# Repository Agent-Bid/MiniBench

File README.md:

# MiniBench

A compact USB-C powered bench power supply board designed to provide common rail voltages directly from your laptop or a USB-C power adapter.

## Features
- **USB-C Input:** Convenient power sourcing from modern laptops and chargers.
- **Triple Voltage Output:** Provides stable power rails for most low-power electronics development:
  - **5.0V**
  - **3.3V**
  - **1.8V**
- **Compact Form Factor:** Small enough to fit in a pocket or a small electronics kit.

## Usage
Simply plug into a USB-C port to provide power to the onboard regulators, then use the designated headers/pads to power your breadboard or prototype.

## License
Licensed under the MIT License (see LICENSE file for details).

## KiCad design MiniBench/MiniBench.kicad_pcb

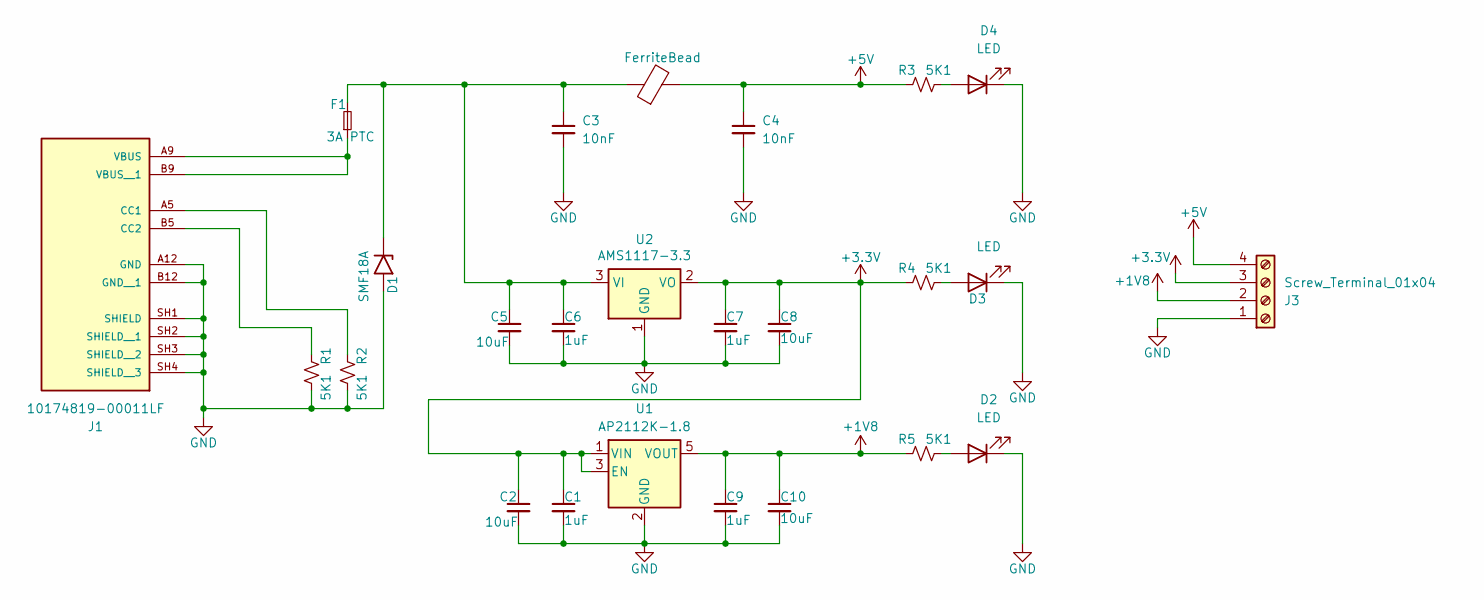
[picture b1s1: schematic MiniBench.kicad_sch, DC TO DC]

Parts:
C1, C6, C7, C9: 1uF; C_0603_1608Metric
C2, C5, C8, C10: 10uF; C_0603_1608Metric
C3, C4: 10nF; C_0603_1608Metric
D1: SMF18A; D_1206_3216Metric
D2, D3, D4: LED; LED_0603_1608Metric
F1: 3A PTC; Fuse_1206_3216Metric
FB1: FerriteBead; C_0603_1608Metric
J1: 10174819-00011LF; AMPHENOL_10174819-00011LF; PARTREV A
J3: Screw_Terminal_01x04; TerminalBlock_Xinya_XY308-2.54-4P_1x04_P2.54mm_Horizontal
R1, R2, R3, R4, R5: 5K1; R_0603_1608Metric
U1: AP2112K-1.8; SOT-23-5
U2: AMS1117-3.3; SOT-223-3_TabPin2

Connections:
+1V8: C9.1, C10.1, J3.2, R5.1, U1.5 (VOUT)
+3.3V: C1.1, C2.1, C7.1, C8.1, J3.3, R4.1, U1.1 (VIN), U1.3 (EN), U2.2 (VO)
+5V: C4.1, FB1.2, J3.4, R3.1
GND: C1.2, C2.2, C3.2, C4.2, C5.2, C6.2, C7.2, C8.2, C9.2, C10.2, D1.2 (A2), D2.1 (K), D3.1 (K), D4.1 (K), J1.A12 (GND), J1.B12 (GND__1), J1.SH1 (SHIELD), J1.SH2 (SHIELD__1), J1.SH3 (SHIELD__2), J1.SH4 (SHIELD__3), J3.1, R1.2, R2.2, U1.2 (GND), U2.1 (GND)
unnamed: C3.1, C5.1, C6.1, D1.1 (A1), F1.2, FB1.1, U2.3 (VI)
unnamed: D2.2 (A), R5.2
unnamed: D3.2 (A), R4.2
unnamed: D4.2 (A), R3.2
unnamed: J1.A5 (CC1), R2.1
unnamed: J1.B5 (CC2), R1.1
unnamed: F1.1, J1.A9 (VBUS), J1.B9 (VBUS__1)

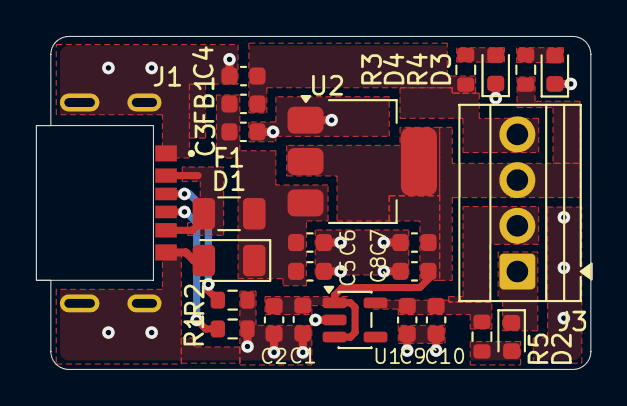
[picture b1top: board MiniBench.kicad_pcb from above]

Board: 2 copper layers, 30.8 x 18.5 mm, 25 parts (0 on the bottom side), 11 nets.

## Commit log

2026-03-01 Update README with project features and status
2026-03-01 Add schematic image and remove project status section
